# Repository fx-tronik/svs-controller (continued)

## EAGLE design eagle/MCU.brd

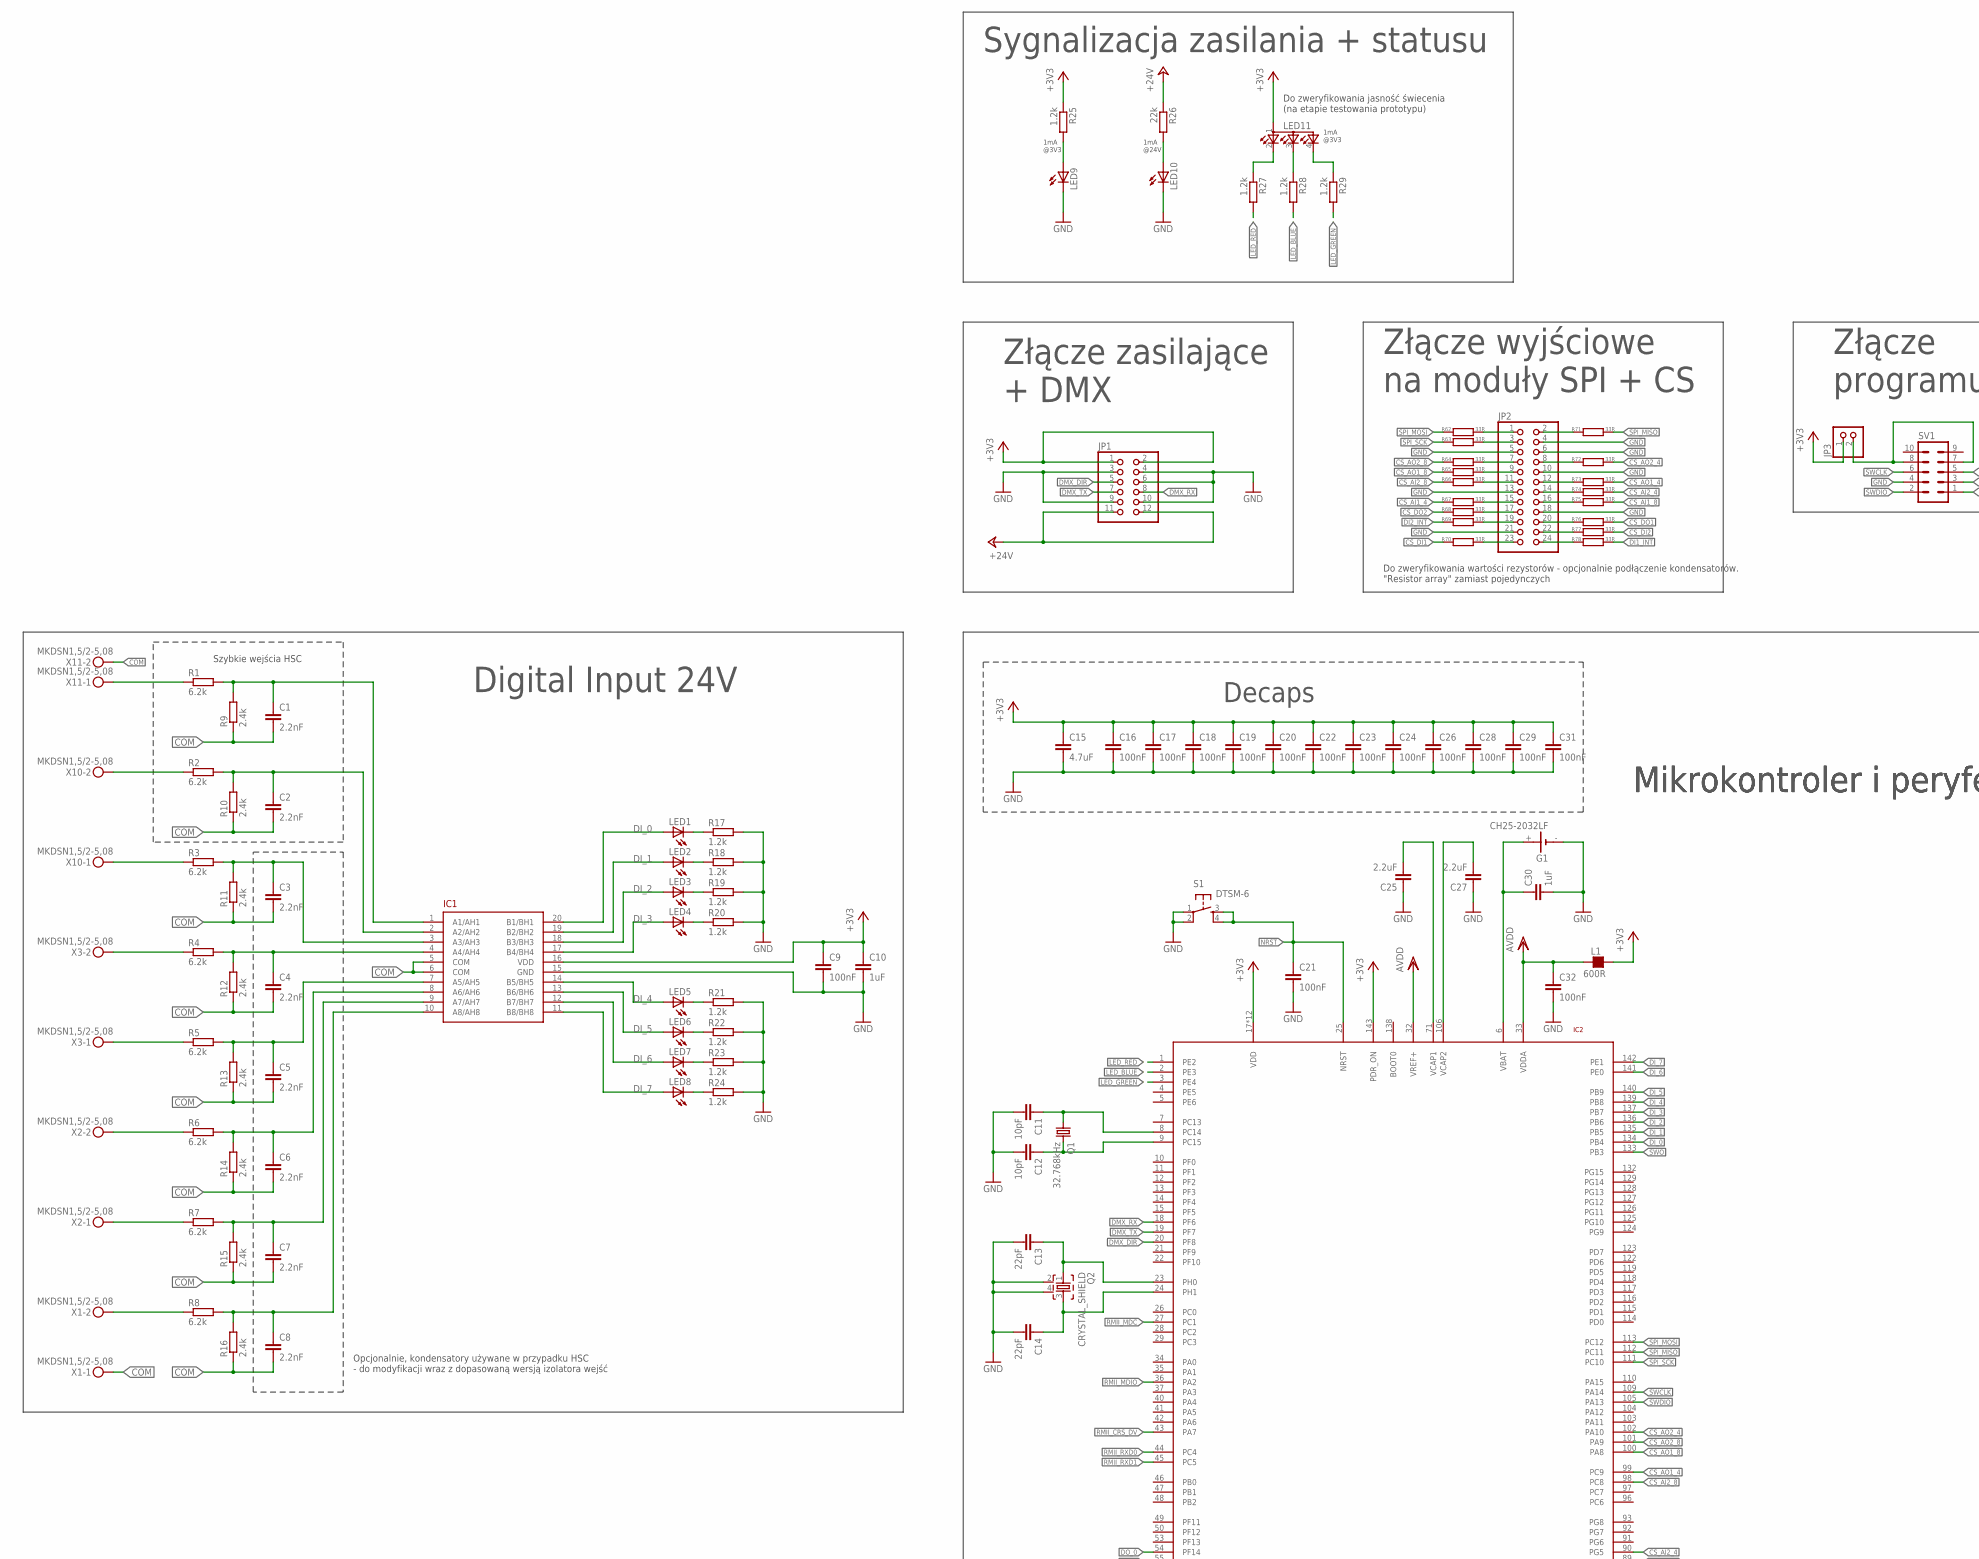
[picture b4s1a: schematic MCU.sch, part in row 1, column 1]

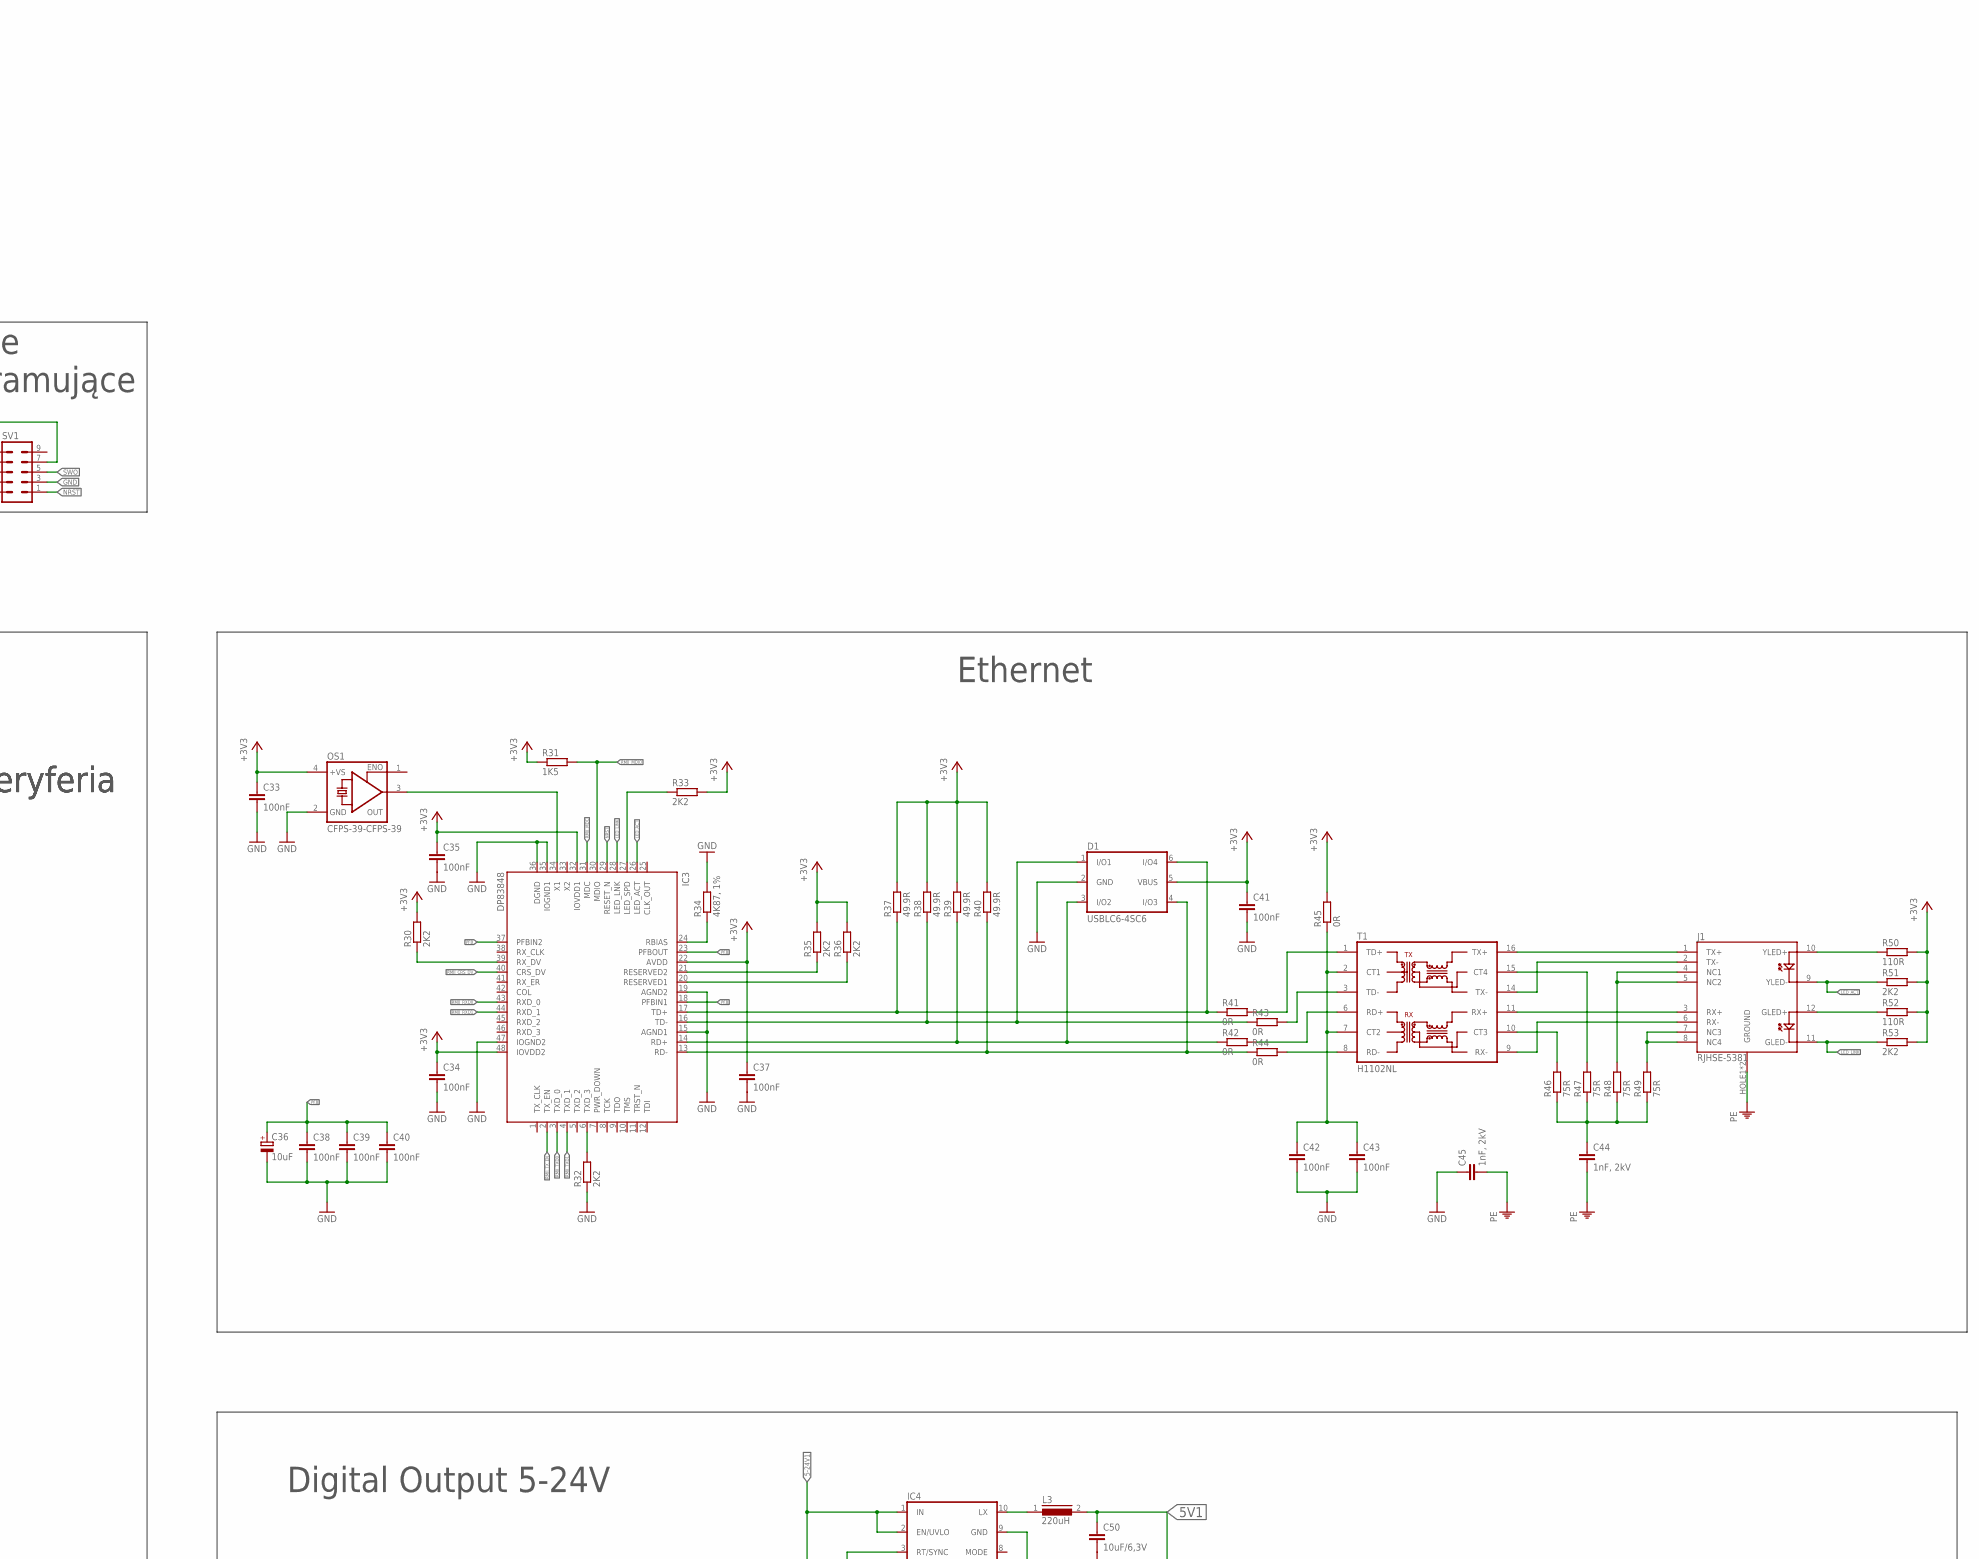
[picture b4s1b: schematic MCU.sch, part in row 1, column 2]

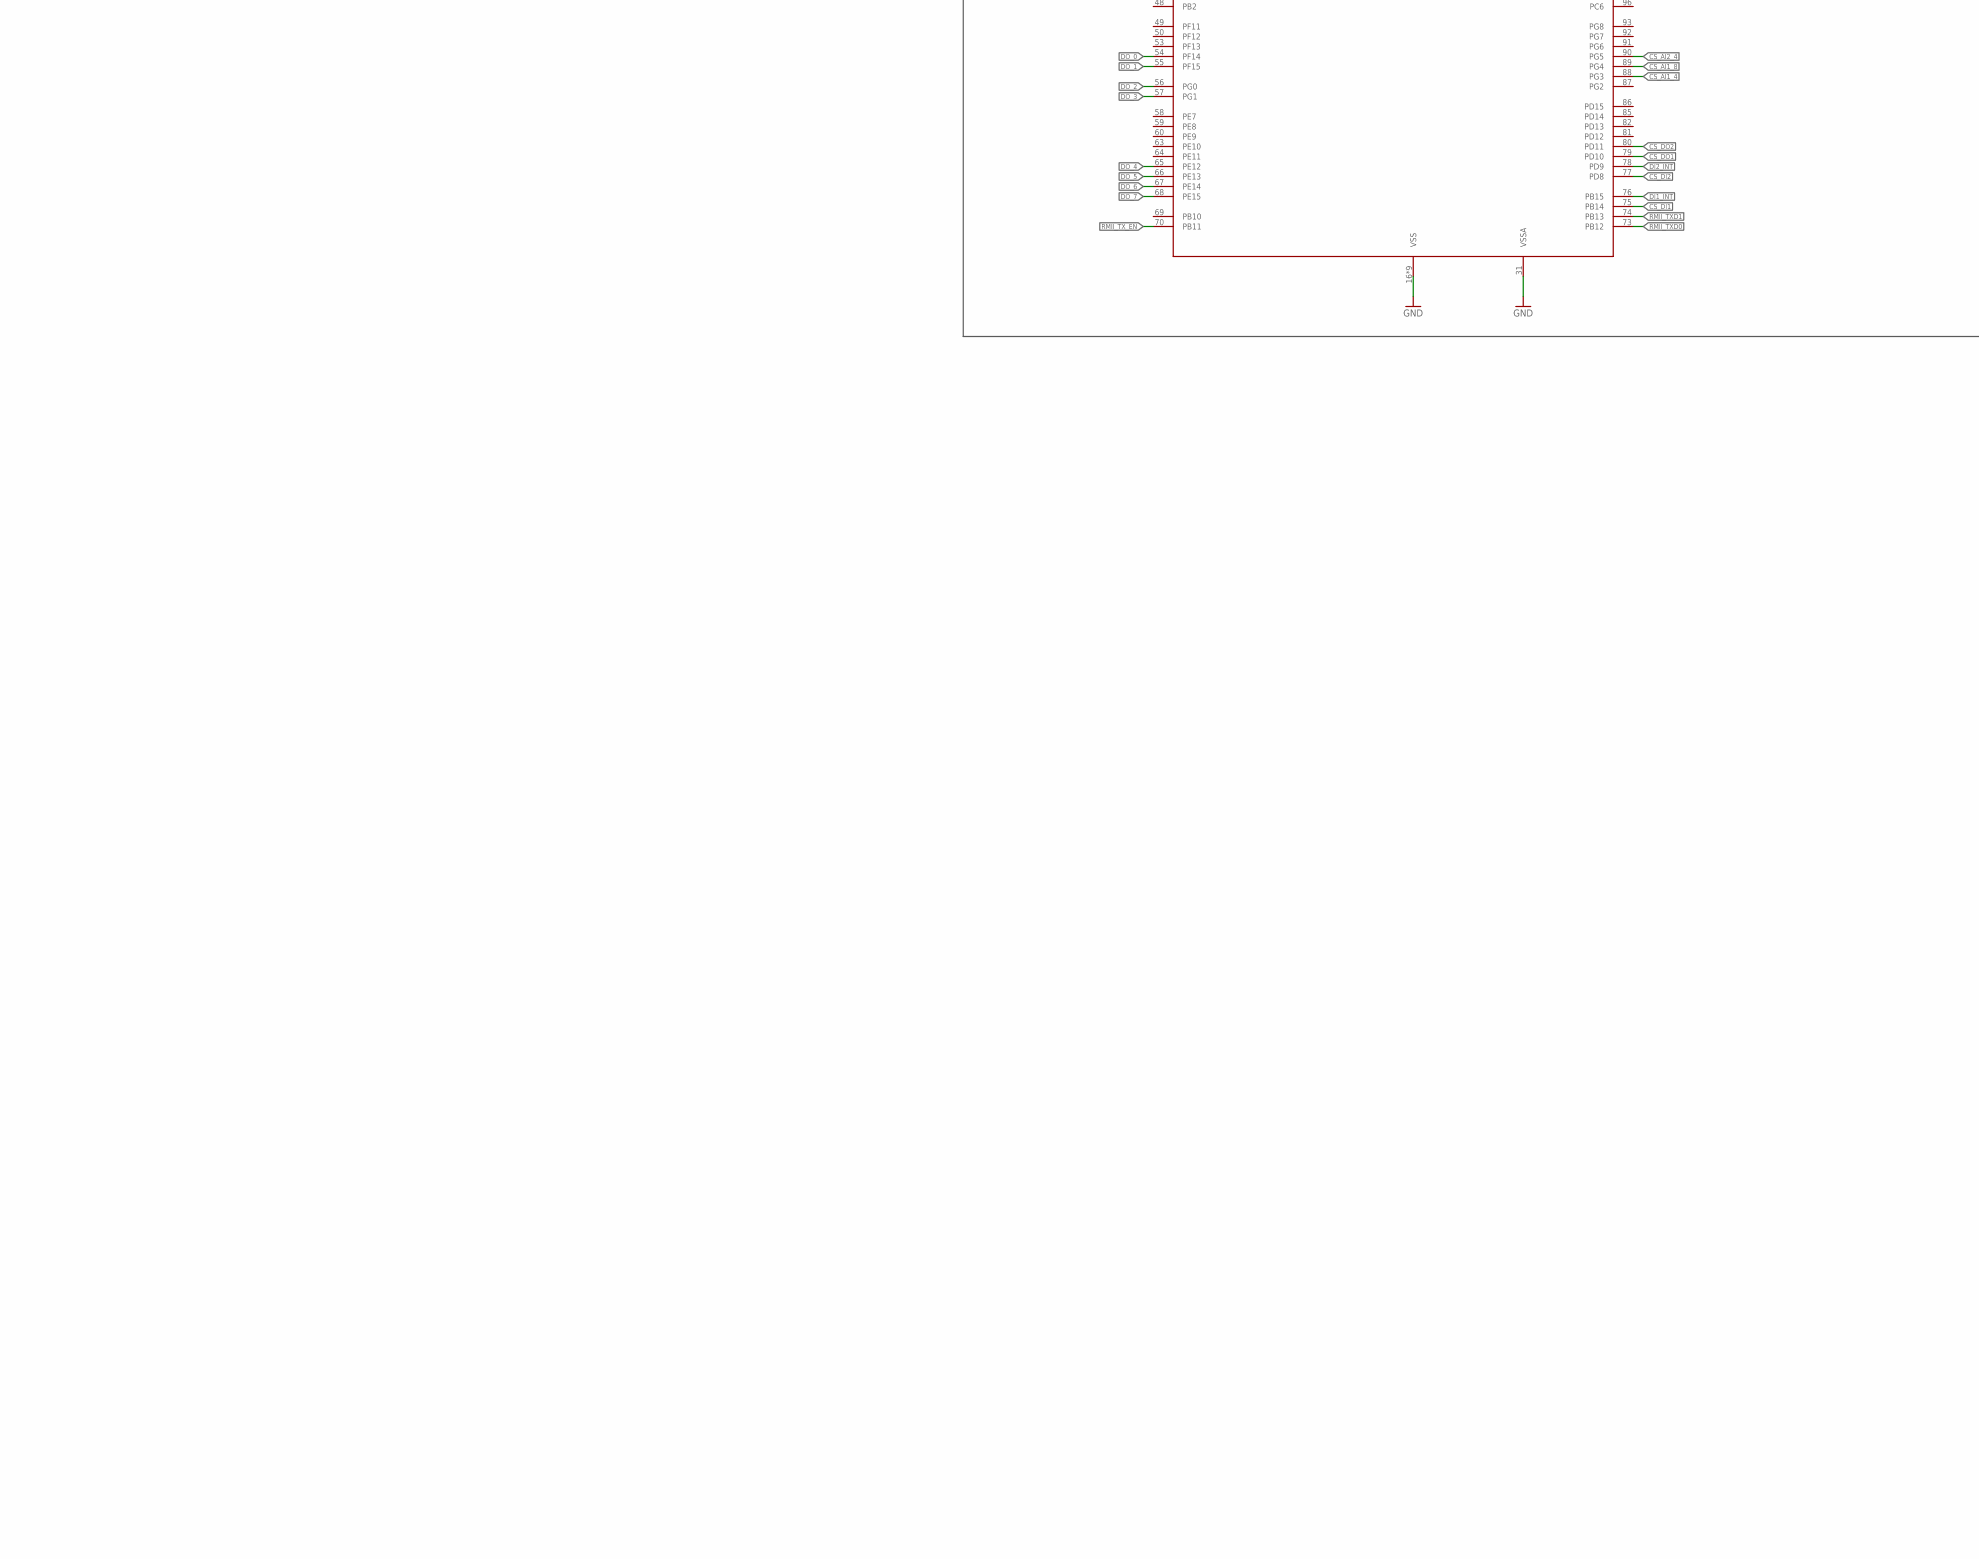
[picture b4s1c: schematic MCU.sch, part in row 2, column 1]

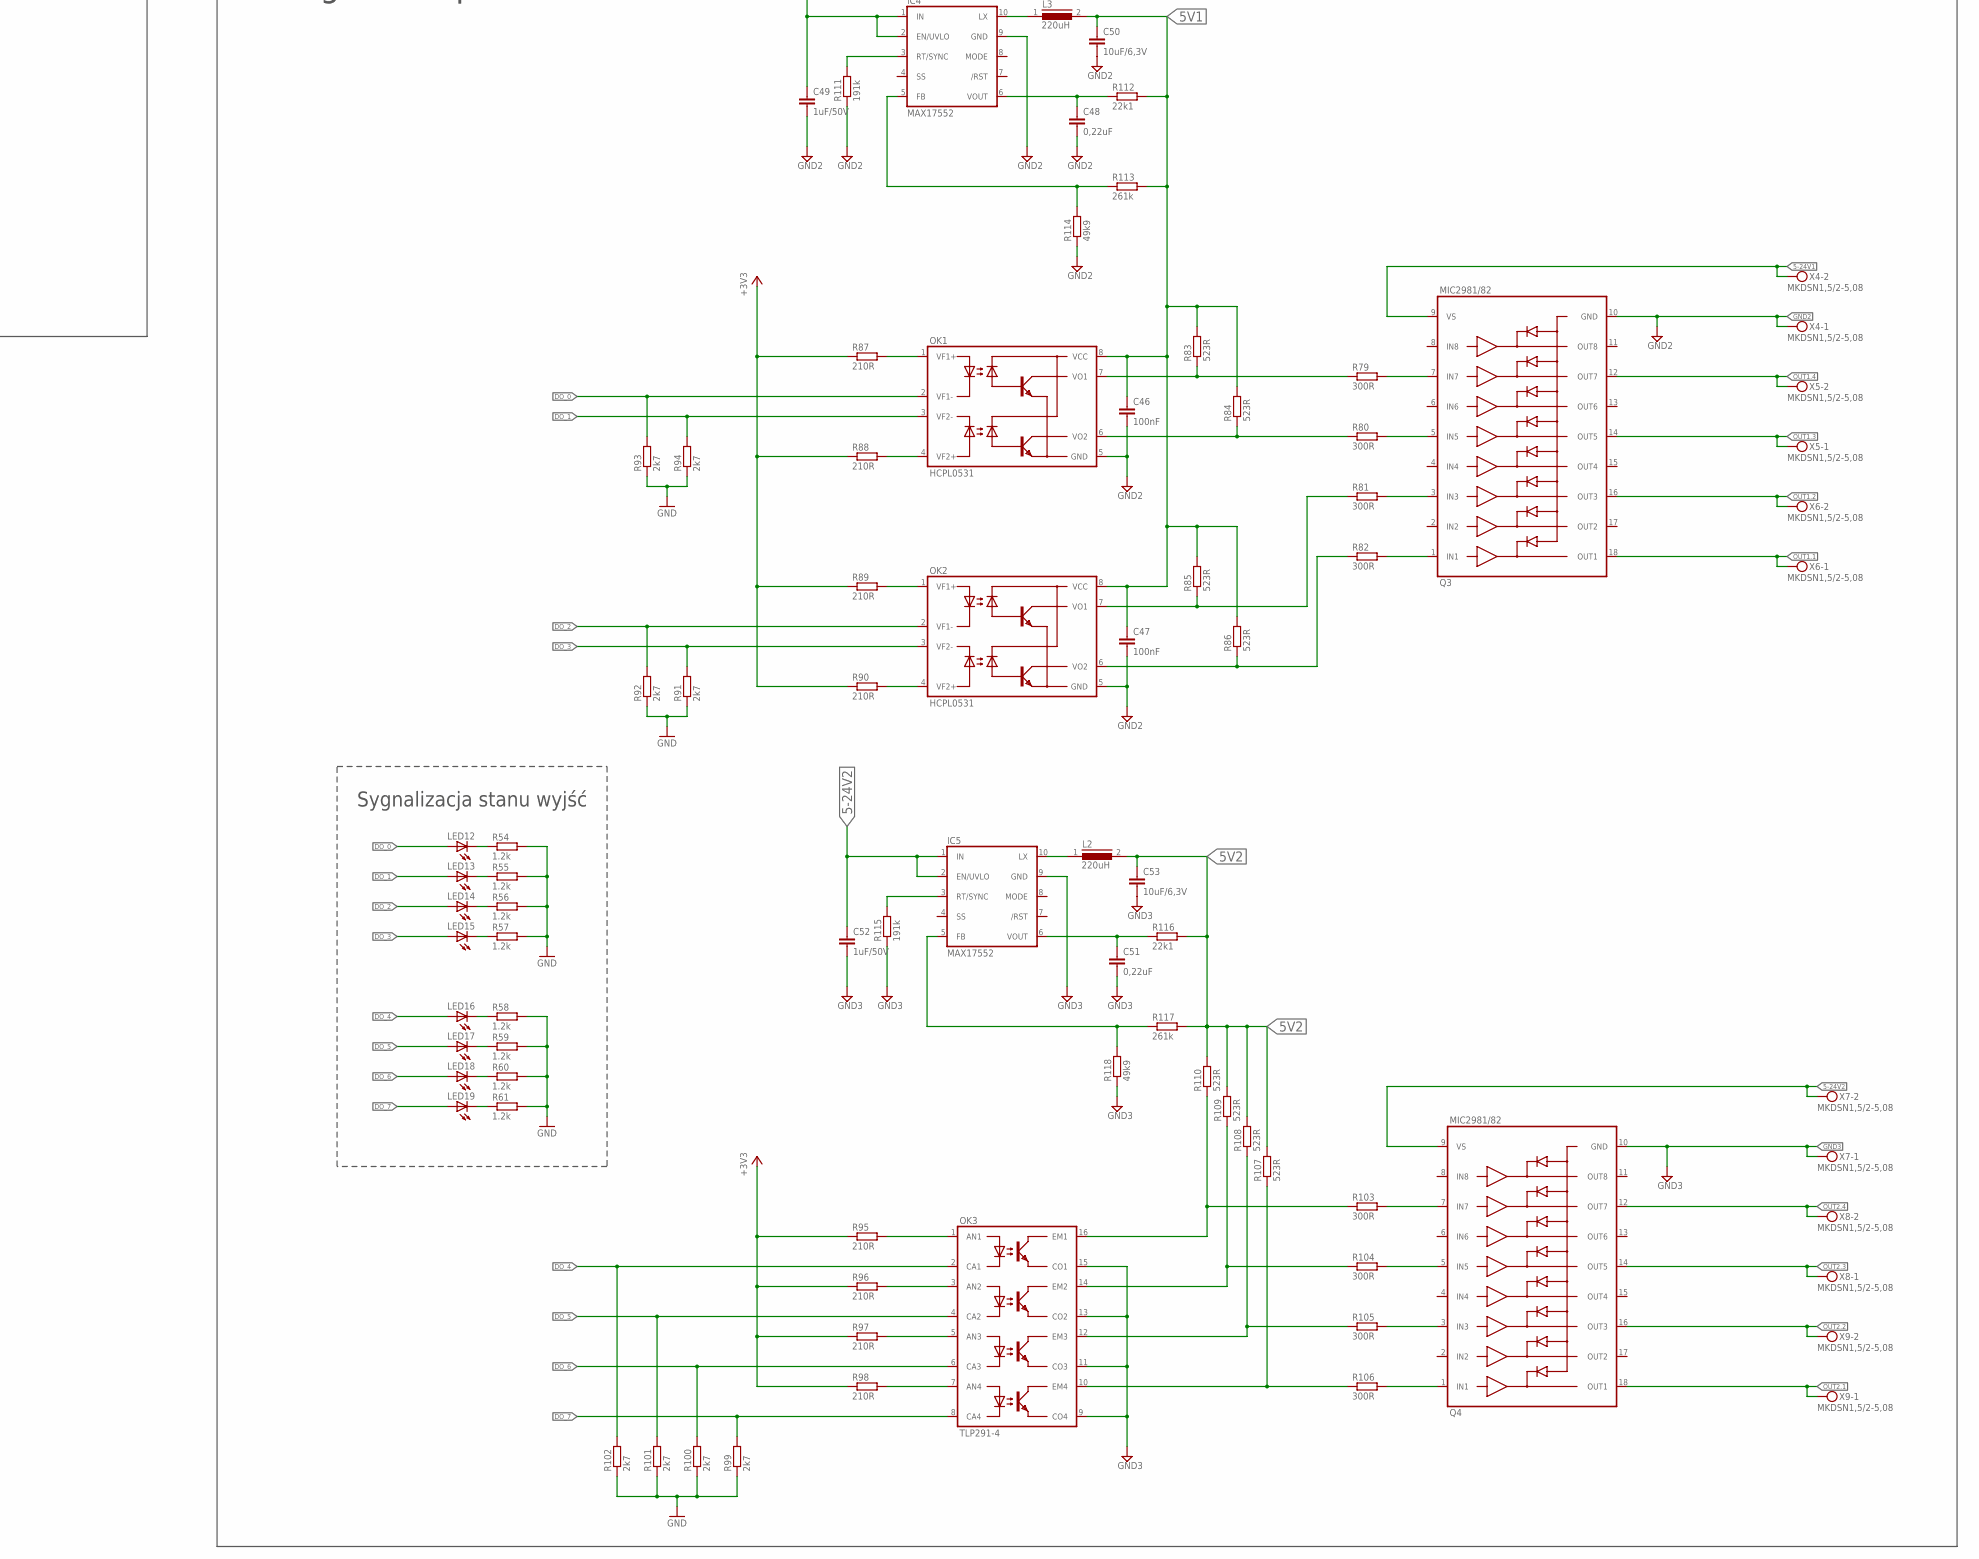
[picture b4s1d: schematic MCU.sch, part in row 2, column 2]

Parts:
C1, C2, C3, C4, C5, C6, C7, C8: 2.2nF; C0805; MPN 06035C222JAT2A
C9, C16, C17, C18, C19, C20, C21, C22, C23, C24, C26, C28, C29, C31, C32: 100nF; C0603K; MPN 06033C104KAT2A
C10, C30: 1uF; C0603K; MPN 0603YC105KAT4A
C11, C12: 10pF; C0603K; MPN 06035A100JAT2A
C13, C14: 22pF; C0603K; MPN 06035A220JAT2A
C15: 4.7uF; C0603K; MPN 0603ZD475KAT2A
C25, C27: 2.2uF; C0603K; MPN 06036C225KAT2A
C33, C34, C35, C37, C38, C39, C40, C41, C42, C43, C46, C47: 100nF; C0603; MPN 06033C104KAT2A
C36: 10uF; SMC_A; MPN F931A106MAA
C44, C45: 1nF, 2kV; C1206; MPN VJ1206Y102MXFAT4X
C48, C51: 0,22uF; C0603; MPN 0603ZC224KAT9A
C49, C52: 1uF/50V; C1206; MPN 12065C105M4Z2A
C50, C53: 10uF/6,3V; C1206; MPN 12066G106ZAT4A
D1: USBLC6-4SC6; SOT23-6; MPN USBLC6-4SC6
G1: CH25-2032LF; MPN CH25-2032
IC1: SI8382P-IU; QSOP-20; MPN SI8382P-IU
IC2: STM32F429ZILQFP144; LQFP144; MPN STM32F429ZIT6
IC3: DP83848; LQFP48; MPN DP83848CVV/NOPB
IC4, IC5: MAX17552; TSSOP-10(10UMAX); MPN MAX17552AUB+
J1: RJHSE-5381; MAGJACK-19938; MPN RJHSE-5381
JP1: PINHD-2X6; 2X06; MPN ZL2019-40
JP2: PINHD-2X12; 2X12; MPN ZL2019-40
JP3: PINHD-1X2; 1X02; MPN DS1021-1*20SF1-5
L1: 600R; L0603; MPN MMZ1608S601ATD25
L2, L3: 220uH; SRR4528A; MPN SRR4528A-221M
LED1, LED2, LED3, LED4, LED5, LED6, LED7, LED8, LED12, LED13, LED14, LED15, LED16, LED17, LED18, LED19: LEDCHIP-LED0603; CHIP-LED0603; MPN APTD1608LCGCK
LED9, LED10: LEDCHIP-LED0603; CHIP-LED0603; MPN APTD1608LSURCK
LED11: APHF1608SEEQBDZGKC; MPN APHF1608SEEQBDZGKC
OK1, OK2: HCPL0531; SOIC08; MPN HCPL-0531-500E
OK3: TLP291-4; SO16; MPN TLP291-4(GB,E)
OS1: CFPS-39-CFPS-39; 3.4X2.7-4-PAD; MPN LFSPXO025560
Q1: 32.768kHz; CRYSTAL_3.5X1.5; MPN ECS-.327-9-34QCS-TR
Q2: CRYSTAL_SHIELD; CRYSTAL_5X3.2; MPN LFXTAL059158
Q3, Q4: MIC2981/82; SOP18; MPN MIC2981/82YWM
R1, R2, R3, R4, R5, R6, R7, R8: 6.2k; R1206; MPN RC1206JR-076K2L
R9, R10, R11, R12, R13, R14, R15, R16: 2.4k; R1206; MPN RC1206JR-072K4L
R17, R18, R19, R20, R21, R22, R23, R24, R25, R27, R28, R29, R54, R55, R56, R57, R58, R59, R60, R61: 1.2k; R0603; MPN RC0603FR-071K2L
R26: 22k; R0603; MPN AC0603FR-0722K1L
R30, R32, R33, R35, R36, R51, R53: 2K2; R0603; MPN RC0603FR-072K2P
R31: 1K5; R0603; MPN RC0603FR-071K5P
R34: 4K87, 1%; R0603; MPN AC0603FR-074K87L
R37, R38, R39, R40: 49.9R; R0603; MPN CR0603-FX-49R9GLF
R41, R42, R43, R44, R45: 0R; R0603; MPN RC0603JR-070RL
R46, R47, R48, R49: 75R; R0603; MPN RC0603JR-0775RL
R50, R52: 110R; R0603; MPN RC0603FR-07110RL
R62, R63, R64, R65, R66, R67, R68, R69, R70, R71, R72, R73, R74, R75, R76, R77, R78: 33R; R0603; MPN RC0603FR-071K2L
R79, R80, R81, R82, R103, R104, R105, R106: 300R; R0603; MPN AC0603FR-07300RL
R83, R84, R85, R86, R107, R108, R109, R110: 523R; R0603; MPN RC0603FR-07523RL
R87, R88, R89, R90, R95, R96, R97, R98: 210R; R0603; MPN CR0603-FX-2100ELF
R91, R92, R93, R94, R99, R100, R101, R102: 2k7; R0603; MPN RC0603JR-072K7L
R111, R115: 191k; R0603; MPN AC0603FR-07191KL
R112, R116: 22k1; R0603; MPN AC0603FR-0722K1L
R113, R117: 261k; R0603; MPN CR0603-FX-2613ELF
R114, R118: 49k9; R0603; MPN CRCW060349K9FKEB
S1: DTSM-6; MPN DTSM-63N-V-B
SV1: ML10; MPN 61201021621
T1: H1102NL; HXXXX; MPN H1102NL
X1, X2, X3, X4, X5, X6, X7, X8, X9, X10, X11: MKDSN1,5/2-5,08; MPN TB-5.08-P-2P/BL

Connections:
5-24V1: C49.1, IC4.1 (IN), IC4.2 (EN/UVLO), Q3.9 (VS), X4.2
5-24V2: C52.1, IC5.1 (IN), IC5.2 (EN/UVLO), Q4.9 (VS), X7.2
5V1: C46.1, C47.1, C50.1, L3.2, OK1.8 (VCC), OK2.8 (VCC), R83.2, R84.2, R85.2, R86.2, R112.2, R113.2
5V2: C53.1, L2.2, R107.2, R108.2, R109.2, R110.2, R116.2, R117.2
+3V3: C9.1, C10.1, C15.1, C16.1, C17.1, C18.1, C19.1, C20.1, C22.1, C23.1, C24.1, C26.1, C28.1, C29.1, C31.1, C33.1, C34.1, C35.1, C37.1, C41.1, D1.5 (VBUS), IC1.16 (VDD), IC2.17 (VDD), IC2.30 (VDD), IC2.39 (VDD), IC2.52 (VDD), IC2.62 (VDD), IC2.72 (VDD), IC2.84 (VDD), IC2.95 (VDD), IC2.108 (VDD), IC2.121 (VDD), IC2.131 (VDD), IC2.143 (PDR_ON), IC2.144 (VDD), IC3.22 (AVDD), IC3.32 (IOVDD1), IC3.48 (IOVDD2), JP1.1, JP1.2, JP3.1, L1.2, LED11.1 (A), OS1.4 (VDD), R25.1, R30.2, R31.1, R33.2, R35.2, R36.2, R37.2, R38.2, R39.2, R40.2, R45.2, R50.2, R51.2, R52.2, R53.2, R87.1, R88.1, R89.1, R90.1, R95.1, R96.1, R97.1, R98.1
+24V: JP1.11, JP1.12, R26.1
COM: C1.2, C2.2, C3.2, C4.2, C5.2, C6.2, C7.2, C8.2, IC1.5 (COM), IC1.6 (COM), R9.1, R10.1, R11.1, R12.1, R13.1, R14.1, R15.1, R16.1, X1.1, X11.2
CS_AI1_4: IC2.88 (PG3), R67.1
CS_AI1_8: IC2.89 (PG4), R75.2
CS_AI2_4: IC2.90 (PG5), R74.2
CS_AI2_8: IC2.98 (PC8), R66.1
CS_AO1_4: IC2.99 (PC9), R73.2
CS_AO1_8: IC2.100 (PA8), R65.1
CS_AO2_4: IC2.102 (PA10), R72.2
CS_AO2_8: IC2.101 (PA9), R64.1
CS_DI1: IC2.75 (PB14), R70.1
CS_DI2: IC2.77 (PD8), R77.2
CS_DO1: IC2.79 (PD10), R76.2
CS_DO2: IC2.80 (PD11), R68.1
DI1_INT: IC2.76 (PB15), R78.2
DI2_INT: IC2.78 (PD9), R69.1
DI_0: IC1.20 (B1/BH1), IC2.134 (PB4), LED1.A
DI_1: IC1.19 (B2/BH2), IC2.135 (PB5), LED2.A
DI_2: IC1.18 (B3/BH3), IC2.136 (PB6), LED3.A
DI_3: IC1.17 (B4/BH4), IC2.137 (PB7), LED4.A
DI_4: IC1.14 (B5/BH5), IC2.139 (PB8), LED5.A
DI_5: IC1.13 (B6/BH6), IC2.140 (PB9), LED6.A
DI_6: IC1.12 (B7/BH7), IC2.141 (PE0), LED7.A
DI_7: IC1.11 (B8/BH8), IC2.142 (PE1), LED8.A
DMX_DIR: IC2.20 (PF8), JP1.5
DMX_RX: IC2.18 (PF6), JP1.8
DMX_TX: IC2.19 (PF7), JP1.7
DO_0: IC2.54 (PF14), LED12.A, OK1.2 (VF1-), R93.2
DO_1: IC2.55 (PF15), LED13.A, OK1.3 (VF2-), R94.2
DO_2: IC2.56 (PG0), LED14.A, OK2.2 (VF1-), R92.2
DO_3: IC2.57 (PG1), LED15.A, OK2.3 (VF2-), R91.2
DO_4: IC2.65 (PE12), LED16.A, OK3.2 (CA1), R102.2
DO_5: IC2.66 (PE13), LED17.A, OK3.4 (CA2), R101.2
DO_6: IC2.67 (PE14), LED18.A, OK3.6 (CA3), R100.2
DO_7: IC2.68 (PE15), LED19.A, OK3.8 (CA4), R99.2
GND: C9.2, C10.2, C11.2, C12.2, C13.2, C14.2, C15.2, C16.2, C17.2, C18.2, C19.2, C20.2, C21.2, C22.2, C23.2, C24.2, C25.1, C26.2, C27.1, C28.2, C29.2, C30.2, C31.2, C32.2, C33.2, C34.2, C35.2, C36.-, C37.2, C38.2, C39.2, C40.2, C41.2, C42.2, C43.2, C45.1, D1.2 (GND), G1.-, IC1.15 (GND), IC2.16 (VSS), IC2.31 (VSSA), IC2.38 (VSS), IC2.51 (VSS), IC2.61 (VSS), IC2.83 (VSS), IC2.94 (VSS), IC2.107 (VSS), IC2.120 (VSS), IC2.130 (VSS), IC3.15 (AGND1), IC3.19 (AGND2), IC3.35 (IOGND1), IC3.36 (DGND), IC3.47 (IOGND2), JP1.3, JP1.4, JP1.6, JP1.9, JP1.10, JP2.4, JP2.5, JP2.6, JP2.10, JP2.13, JP2.18, JP2.21, LED9.C, LED10.C, OS1.2 (VSS), Q2.2, Q2.4, R17.2, R18.2, R19.2, R20.2, R21.2, R22.2, R23.2, R24.2, R32.1, R34.2, R54.2, R55.2, R56.2, R57.2, R58.2, R59.2, R60.2, R61.2, R91.1, R92.1, R93.1, R94.1, R99.1, R100.1, R101.1, R102.1, S1.1, S1.2, SV1.3, SV1.4
GND2: C46.2, C47.2, C48.2, C49.2, C50.2, IC4.9 (GND), OK1.5 (GND), OK2.5 (GND), Q3.10 (GND), R111.1, R114.1, X4.1
GND3: C51.2, C52.2, C53.2, IC5.9 (GND), OK3.9 (CO4), OK3.11 (CO3), OK3.13 (CO2), OK3.15 (CO1), Q4.10 (GND), R115.1, R118.1, X7.1
LED_ACT: IC3.26 (LED_ACT), J1.9 (YLED-), R51.1
LED_BLUE: IC2.2 (PE3), R28.2
LED_GREEN: IC2.3 (PE4), R29.2
LED_LINK: IC3.28 (LED_LNK), J1.11 (GLED-), R53.1
LED_RED: IC2.1 (PE2), R27.2
unnamed: LED11.2 (CRED), R27.1
unnamed: C25.2, IC2.71 (VCAP1)
unnamed: C27.2, IC2.106 (VCAP2)
unnamed: C11.1, IC2.8 (PC14), Q1.1
unnamed: C12.1, IC2.9 (PC15), Q1.2
unnamed: LED12.C, R54.1
unnamed: C13.1, IC2.23 (PH0), Q2.1
unnamed: C14.1, IC2.24 (PH1), Q2.3
unnamed: C1.1, IC1.1 (A1/AH1), R1.2, R9.2
unnamed: LED11.3 (CBLUE), R28.1
unnamed: LED1.C, R17.1
unnamed: C2.1, IC1.2 (A2/AH2), R2.2, R10.2
unnamed: LED2.C, R18.1
unnamed: LED3.C, R19.1
unnamed: R1.1, X11.1
unnamed: LED11.4 (CGREEN), R29.1
unnamed: LED4.C, R20.1
unnamed: R2.1, X10.2
unnamed: C3.1, IC1.3 (A3/AH3), R3.2, R11.2
unnamed: R3.1, X10.1
unnamed: C4.1, IC1.4 (A4/AH4), R4.2, R12.2
unnamed: R4.1, X3.2
unnamed: C5.1, IC1.7 (A5/AH5), R5.2, R13.2
unnamed: R5.1, X3.1
unnamed: C6.1, IC1.8 (A6/AH6), R6.2, R14.2
unnamed: R6.1, X2.2
unnamed: C7.1, IC1.9 (A7/AH7), R7.2, R15.2
unnamed: R7.1, X2.1
unnamed: C8.1, IC1.10 (A8/AH8), R8.2, R16.2
unnamed: R8.1, X1.2
unnamed: LED10.A, R26.2
unnamed: LED5.C, R21.1
unnamed: LED6.C, R22.1
unnamed: LED7.C, R23.1
unnamed: LED8.C, R24.1
unnamed: LED13.C, R55.1
unnamed: LED14.C, R56.1
unnamed: LED15.C, R57.1
unnamed: J1.4 (NC1), J1.5 (NC2), R48.2
unnamed: J1.7 (NC3), J1.8 (NC4), R49.2
unnamed: R47.2, T1.15 (CT4)
unnamed: LED9.A, R25.2
unnamed: R46.2, T1.10 (CT3)
unnamed: C44.1, R46.1, R47.1, R48.1, R49.1
unnamed: J1.12 (GLED+), R52.1
unnamed: J1.10 (YLED+), R50.1
unnamed: LED16.C, R58.1
unnamed: LED17.C, R59.1
unnamed: LED18.C, R60.1
unnamed: LED19.C, R61.1
unnamed: C42.1, C43.1, R45.1, T1.2 (CT1), T1.7 (CT2)
unnamed: IC3.21 (RESERVED2), R35.1
unnamed: IC3.20 (RESERVED1), R36.1
unnamed: IC3.24 (RBIAS), R34.1
unnamed: R41.2, T1.1 (TD+)
unnamed: R43.2, T1.3 (TD-)
unnamed: R42.2, T1.6 (RD+)
unnamed: R44.2, T1.8 (RD-)
unnamed: IC3.34 (X1), OS1.3 (OUT)
unnamed: IC3.27 (LED_SPD), R33.1
unnamed: IC3.39 (RX_DV), R30.1
unnamed: IC3.6 (TXD_3), R32.2
unnamed: JP3.2, SV1.7, SV1.8
unnamed: JP2.2, R71.1
unnamed: JP2.8, R72.1
unnamed: JP2.12, R73.1
unnamed: JP2.14, R74.1
unnamed: JP2.16, R75.1
unnamed: JP2.20, R76.1
unnamed: JP2.22, R77.1
unnamed: JP2.3, R63.2
unnamed: JP2.1, R62.2
unnamed: JP2.7, R64.2
unnamed: JP2.9, R65.2
unnamed: JP2.11, R66.2
unnamed: JP2.15, R67.2
unnamed: JP2.17, R68.2
unnamed: JP2.19, R69.2
unnamed: JP2.23, R70.2
unnamed: JP2.24, R78.1
unnamed: OK1.7 (VO1), R79.1, R83.1
unnamed: Q3.7 (IN7), R79.2
unnamed: OK1.6 (VO2), R80.1, R84.1
unnamed: OK2.7 (VO1), R81.1, R85.1
unnamed: OK2.6 (VO2), R82.1, R86.1
unnamed: Q3.5 (IN5), R80.2
unnamed: Q3.3 (IN3), R81.2
unnamed: Q3.1 (IN1), R82.2
unnamed: OK1.1 (VF1+), R87.2
unnamed: OK1.4 (VF2+), R88.2
unnamed: OK2.1 (VF1+), R89.2
unnamed: OK2.4 (VF2+), R90.2
unnamed: OK3.1 (AN1), R95.2
unnamed: OK3.3 (AN2), R96.2
unnamed: OK3.5 (AN3), R97.2
unnamed: OK3.7 (AN4), R98.2
unnamed: Q4.7 (IN7), R103.2
unnamed: Q4.5 (IN5), R104.2
unnamed: Q4.3 (IN3), R105.2
unnamed: Q4.1 (IN1), R106.2
unnamed: OK3.12 (EM3), R105.1, R108.1
unnamed: OK3.14 (EM2), R104.1, R109.1
unnamed: OK3.16 (EM1), R103.1, R110.1
unnamed: OK3.10 (EM4), R106.1, R107.1
unnamed: IC4.3 (RT/SYNC), R111.2
unnamed: IC4.10 (LX), L3.1
unnamed: IC4.5 (FB), R113.1, R114.2
unnamed: C48.1, IC4.6 (VOUT), R112.1
unnamed: IC5.3 (RT/SYNC), R115.2
unnamed: IC5.10 (LX), L2.1
unnamed: IC5.5 (FB), R117.1, R118.2
unnamed: C51.1, IC5.6 (VOUT), R116.1
NRST: C21.1, IC2.25 (NRST), IC3.29 (RESET_N), S1.3, S1.4, SV1.1
OUT1.1: Q3.18 (OUT1), X6.1
OUT1.2: Q3.16 (OUT3), X6.2
OUT1.3: Q3.14 (OUT5), X5.1
OUT1.4: Q3.12 (OUT7), X5.2
OUT2.1: Q4.18 (OUT1), X9.1
OUT2.2: Q4.16 (OUT3), X9.2
OUT2.3: Q4.14 (OUT5), X8.1
OUT2.4: Q4.12 (OUT7), X8.2
PE: C44.2, C45.2, J1.HOLE1 (GROUND), J1.HOLE2 (GROUND)
PFB: C36.+, C38.1, C39.1, C40.1, IC3.18 (PFBIN1), IC3.23 (PFBOUT), IC3.37 (PFBIN2)
RD_N: D1.4 (I/O3), IC3.13 (RD-), R40.1, R44.1
RD_P: D1.3 (I/O2), IC3.14 (RD+), R39.1, R42.1
RMII_CRS_DV: IC2.43 (PA7), IC3.40 (CRS_DV)
RMII_MDC: IC2.27 (PC1), IC3.31 (MDC)
RMII_MDIO: IC2.36 (PA2), IC3.30 (MDIO), R31.2
RMII_RXD0: IC2.44 (PC4), IC3.43 (RXD_0)
RMII_RXD1: IC2.45 (PC5), IC3.44 (RXD_1)
RMII_TXD0: IC2.73 (PB12), IC3.3 (TXD_0)
RMII_TXD1: IC2.74 (PB13), IC3.4 (TXD_1)
RMII_TX_EN: IC2.70 (PB11), IC3.2 (TX_EN)
RX_N: J1.6 (RX-), T1.9 (RX-)
RX_P: J1.3 (RX+), T1.11 (RX+)
SPI_MISO: IC2.112 (PC11), R71.2
SPI_MOSI: IC2.113 (PC12), R62.1
SPI_SCK: IC2.111 (PC10), R63.1
SWCLK: IC2.109 (PA14), SV1.6
SWDIO: IC2.105 (PA13), SV1.2
SWO: IC2.133 (PB3), SV1.5
TD_N: D1.1 (I/O1), IC3.16 (TD-), R38.1, R43.1
TD_P: D1.6 (I/O4), IC3.17 (TD+), R37.1, R41.1
TX_N: J1.2 (TX-), T1.14 (TX-)
TX_P: J1.1 (TX+), T1.16 (TX+)
VBAT: C30.1, G1.+, IC2.6 (VBAT)
VDDA: C32.1, IC2.32 (VREF+), IC2.33 (VDDA), L1.1

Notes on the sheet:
Mikrokontroler i peryferia
Sygnalizacja zasilania + statusu
1mA @3V3
Digital Input 24V
Szybkie wejścia HSC
1mA @24V
Do zweryfikowania jasność świecenia (na etapie testowania prototypu)
Ethernet
Opcjonalnie, kondensatory używane w przypadku HSC - do modyfikacji wraz z dopasowaną wersją izolatora wejść
Złącze zasilające + DMX
Decaps
Złącze wyjściowe na moduły SPI + CS
Złącze programujące
Digital Output 5-24V
Do zweryfikowania wartości rezystorów - opcjonalnie podłączenie kondensatorów. "Resistor array" zamiast pojedynczych
Sygnalizacja stanu wyjść

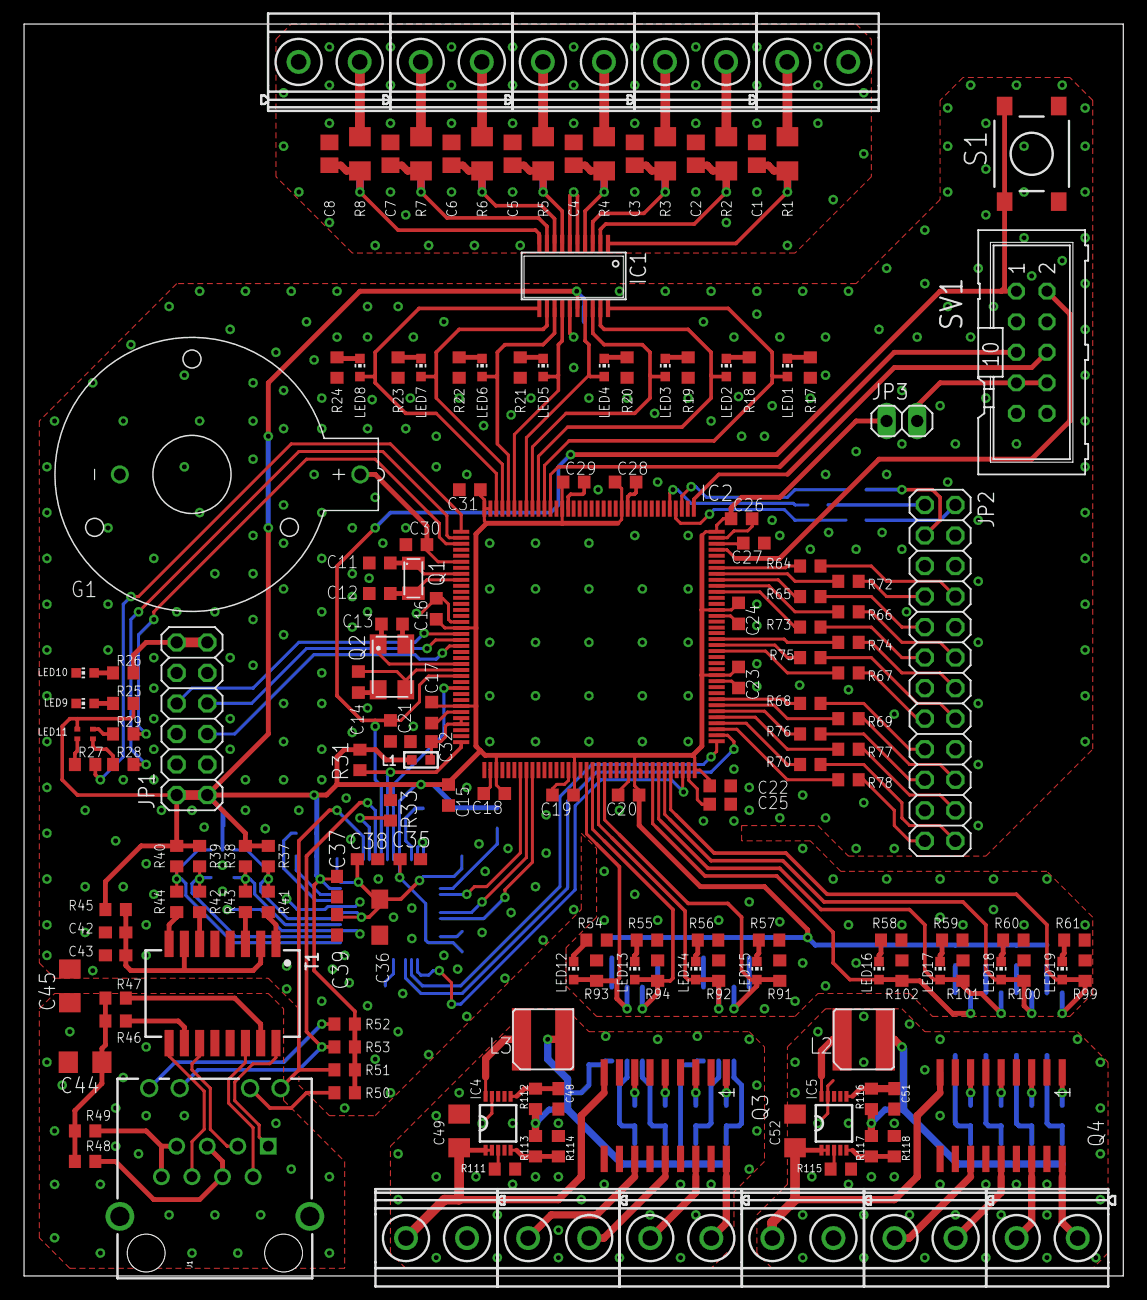
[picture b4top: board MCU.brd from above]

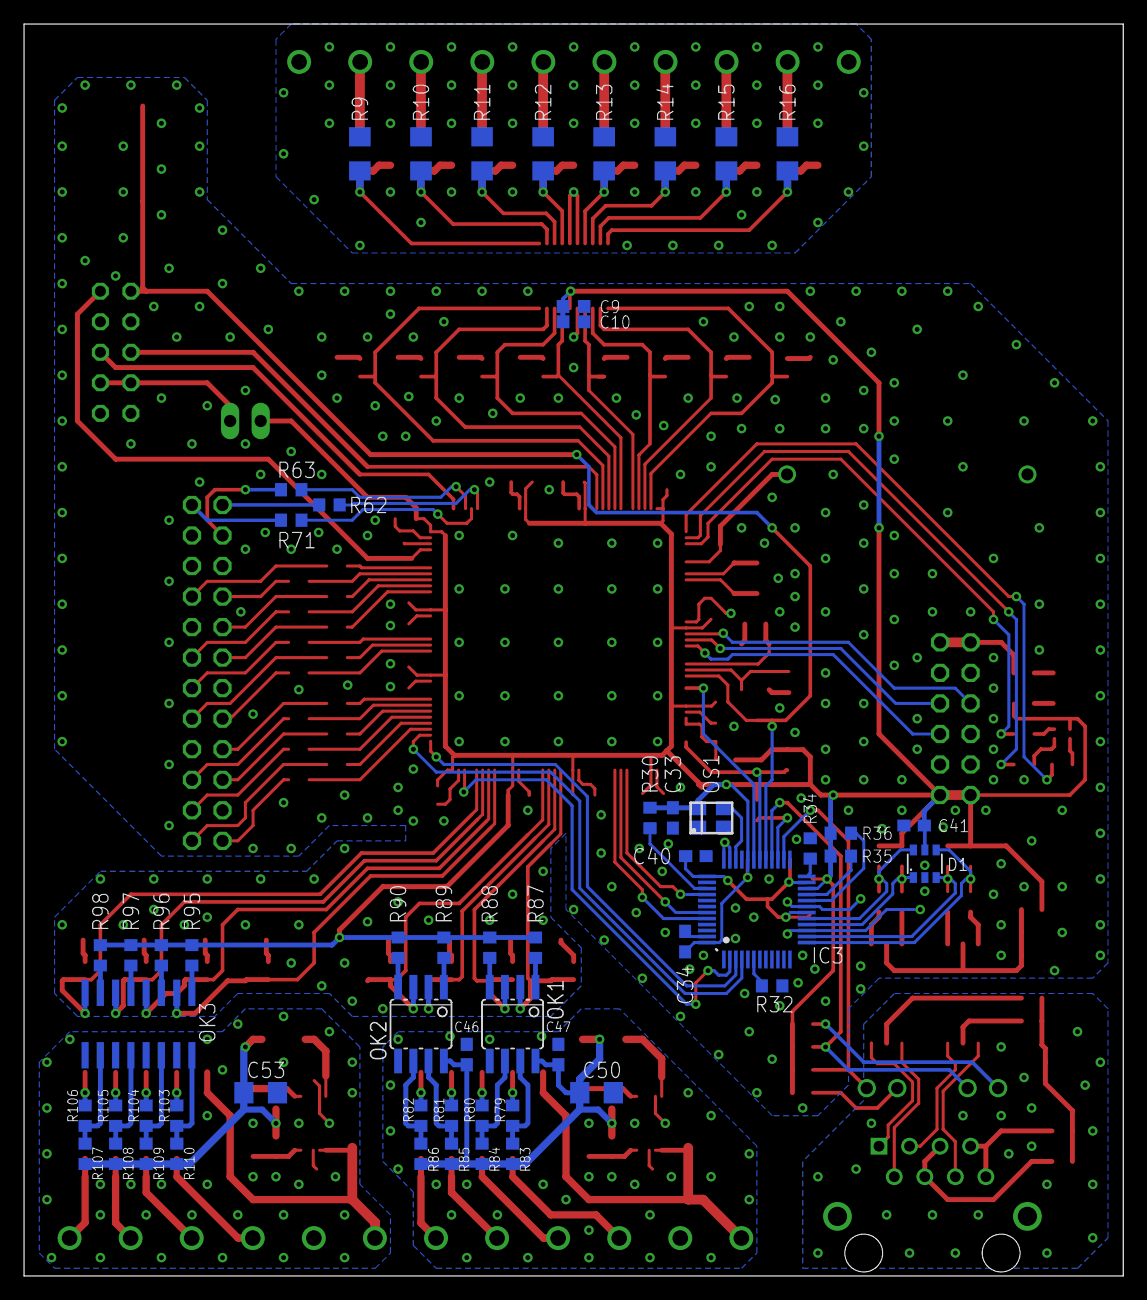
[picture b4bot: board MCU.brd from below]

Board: 2 copper layers, 91.4 x 104.1 mm, 226 parts (56 on the bottom side), 195 nets.

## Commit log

2022-07-01 init
